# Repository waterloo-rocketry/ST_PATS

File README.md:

# ST PATS
Stpats is a system that tracks the location of the rocket and tells us where
and which direction to go to find it.

There are two modes of operation: serial and radio. In serial mode, GPS
coordinate is received from USB serial; in radio mode, GPS coordinate is
received from the radio module.

## Calibration
The on-board compass needs to be calibrated when a firmware is flashed or when
using stpats in a new environment. The compass will not work correctly without
calibration. To enter calibration mode, press the left button. The min/max
value of each axis should appear on the top left of the screen. Rotate the
whole device in every direction so the numbers stabilize, the press the left
button again to save the calibration.

## Radio Telemetry
The radio and serial mode can be toggled using the right button. At the time of
writing, the live telemetry is not done yet, so I used an Arduino to send fake
coordinates at 57600 baud to test serial reading and parsing. In theory,
plugging in configured live telemetry breakout should just work. In reality,
who knows.

## Serial Telemetry
As an alternative to radio telemetry, USB serial can also be used to send GPS
coordinate to stpats. The serial mode can be switched to using the right
button. The GPS message has the format of `[0-9]+.[0-9]*[NSEWM]`, for example:
`12.34N56.78W90M` means 12.34 degrees north, 56.78 degrees west, 90m high. The
altitude information is not used in the calculations so it’s optional.

## aprs2stpats.py
`utils/aprs2stpats.py` can be used to send APRS coordinates to stpats. To use,
install aprspy and bitstring using pip, then follow the steps in
[Receiving APRS Packet](https://uwaterloo.atlassian.net/wiki/spaces/ROCKETRY/pages/43003445444)
to setup and run direwolf TNC as a KISS server.

`usage: aprs2stpats.py [-h] [-H HOST] [-p PORT] [-c CALLSIGN] [-o OUTPUT] [--debug]`

The --host and --port options specifies the KISS TNC server to connect to. By
default, they are 127.0.0.1:8001, which connects to a direwolf instance running
on localhost.

The --callsign option filters the message by sender’s callsign, in case there
are multiple APRS beacons on the same frequency. Note the callsign includes
ssid, for example, VE7OIR-1 instead of just VE7OIR. By default, it forwards all
GPS messages.

The --output option specified the output. By default it is stdout. To send the
output to serial, use --output \\.\COM1 (Windows) or --output /dev/ttyACM0
(Linux), change COM1 or ACM0 to the actual serial port stpats is on.

The --debug options prints additional info to stderr.

## Persistent Location
Press the middle button in either mode to save the current tracking location in
flash so a reset doesn’t lose it. Most useful when one wants to unplug stpats
from computer in serial mode, pressing the middle button before disconnecting
allows one to move around without worrying losing track in case of accidental
reset.

Note: similar to calibration data, flashing a firmware wipes the flash and so
the saved data.

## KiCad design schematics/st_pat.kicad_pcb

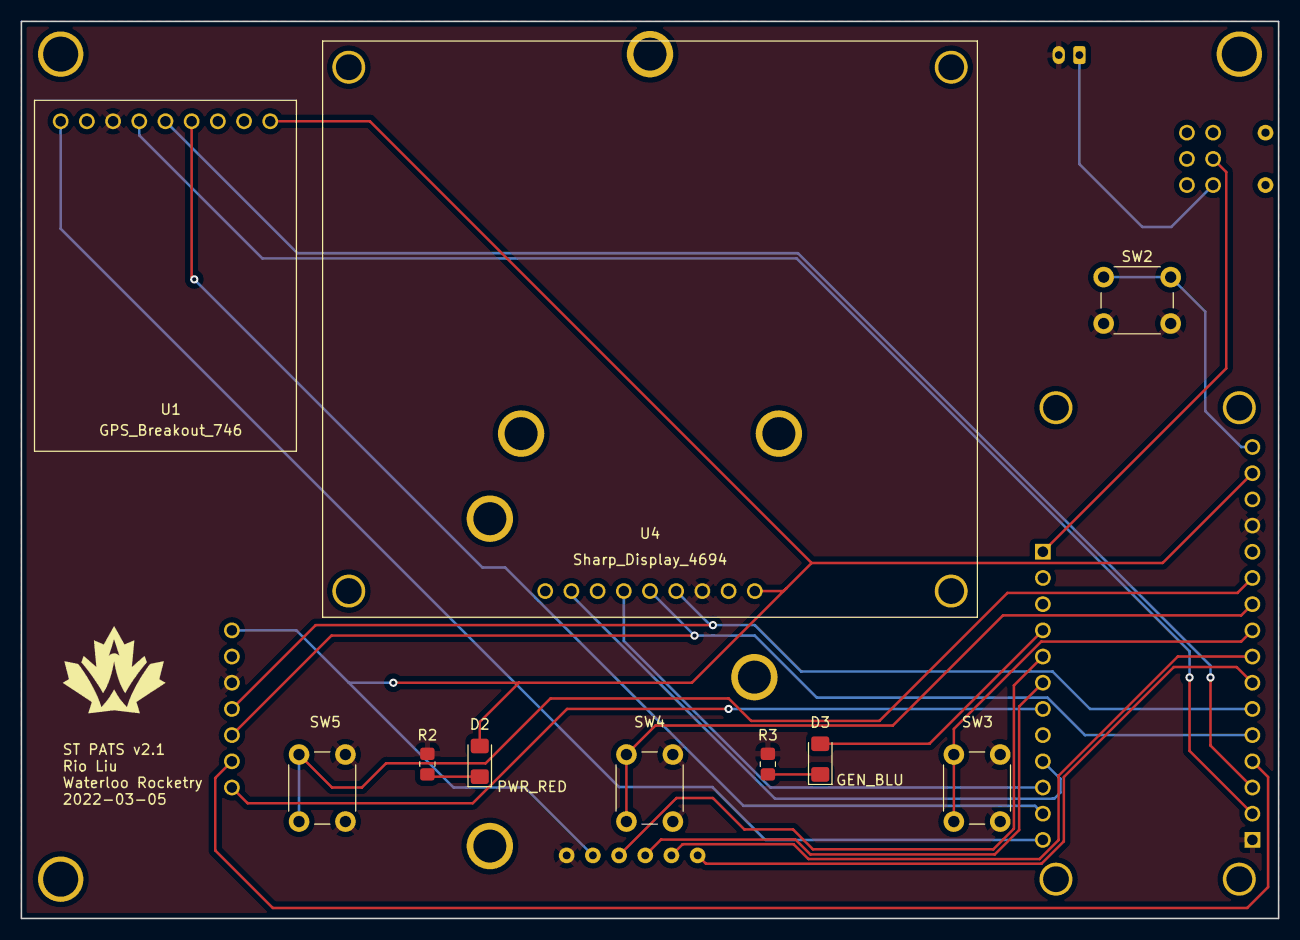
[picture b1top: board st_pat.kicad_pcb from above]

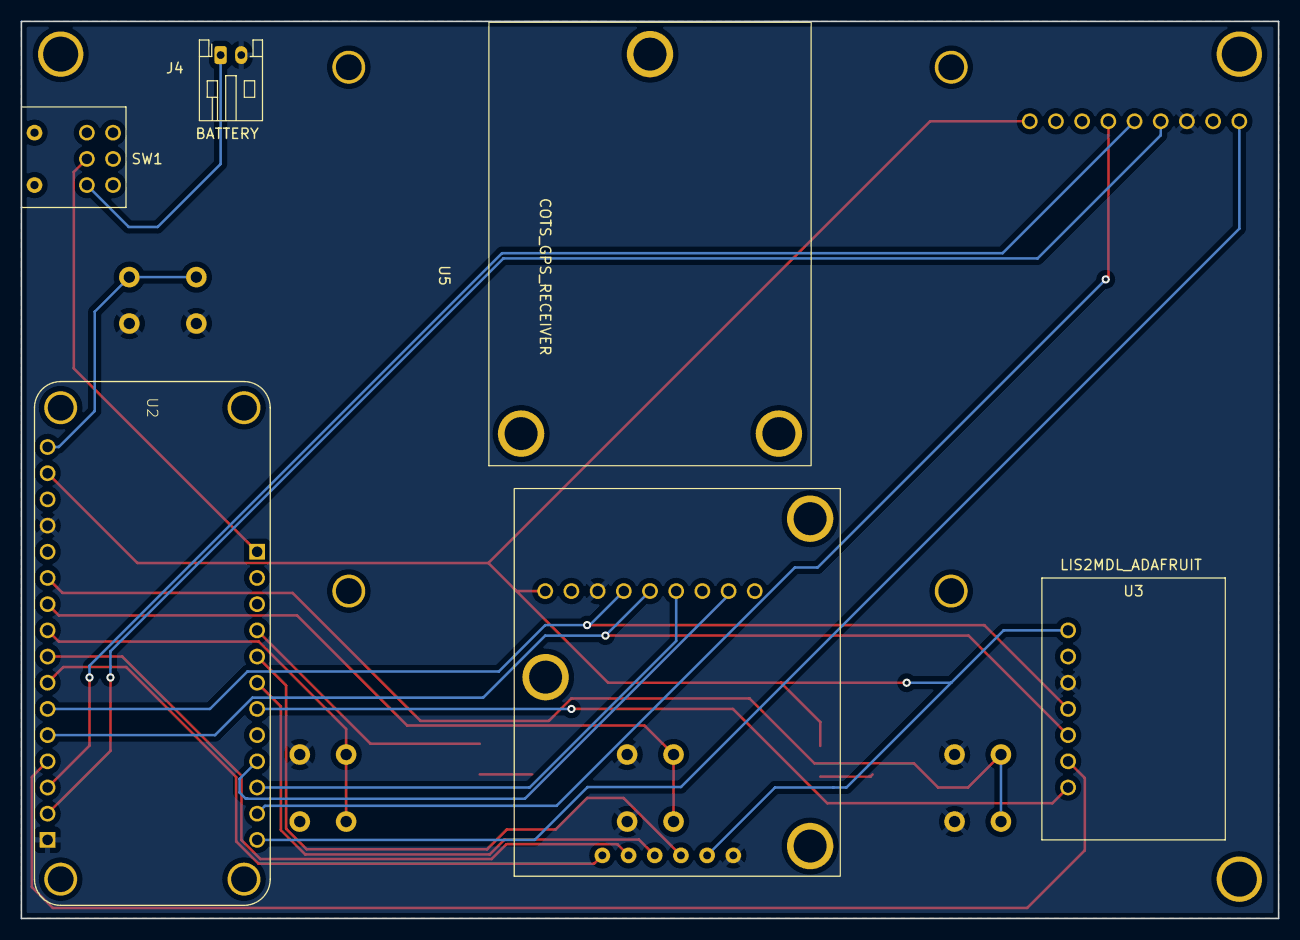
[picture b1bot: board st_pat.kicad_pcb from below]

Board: 2 copper layers, 121.9 x 87.0 mm, 15 parts (5 on the bottom side), 25 nets.

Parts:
D2: PWR_RED; LED_1206_3216Metric_Pad1.42x1.75mm_HandSolder
D3: GEN_BLU; LED_1206_3216Metric_Pad1.42x1.75mm_HandSolder
J4: BATTERY; JST_PH_S2B-PH-K_1x02_P2.00mm_Horizontal
R2: 160; R_0805_2012Metric_Pad1.20x1.40mm_HandSolder
R3: 100; R_0805_2012Metric_Pad1.20x1.40mm_HandSolder
SW1: SW_PWR; SW_Rocker_A22K1H-EA
SW2: BTN_RST; SW_PUSH_6mm
SW3, SW4, SW5: BTN; SW_PUSH_6mm
U1: GPS_Breakout_746
U2: FEATHER_M0_BASIC_PROTO
U3: LIS2MDL_ADAFRUIT; LIS3MDL_ADAFRUIT
U4: Sharp_Display_4694; Sharp_Display
U5: COTS_GPS_RECEIVER; Telemetry_Breakout

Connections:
+3V3: D2.2 (A), U1.9 (3v3), U2.P1_15 (3V3), U3.1 (VCC), U4.1 (VIN), U5.5 (VCC)
+BATT: SW1.5 (B), U2.P2_1 (VBAT)
/BTN_A1: SW5.1, U2.P1_11 (AIN2/EINT/PB08)
/BTN_A2: SW4.1, U2.P1_10 (AIN3/EINT/PB09)
/BTN_A3: SW3.1, U2.P1_9 (AIN4/VREFB/EINT/PA04)
/CPS_CS_D10: U2.P2_7 (PA18/EINT), U3.7 (CS)
/GPS_FIX_D21: U1.6 (FIX), U2.P2_11 (PA23/EINT/I2C/SCL)
/GPS_PPS_D20: U1.1 (PPS), U2.P2_12 (PA22/EINT/I2C/SDA)
/GPS_RX: U1.4 (RX), U2.P1_2 (TX/I2SCK/EINT/PA10)
/GPS_TX: U1.5 (TX), U2.P1_3 (RX/I2SF0/EINT/PA11)
/MISO: U2.P1_4 (MISO/I2C/PA12), U3.6 (SDO)
/MOSI: U2.P1_5 (MOSI/I2SMC/EINT/PB10), U3.5 (SDA), U4.5 (SI)
/RST: SW2.1, U2.P1_16 (~RESET)
/SCK: U2.P1_6 (SCK/I2SCL/EINT/PB11), U3.4 (SCL), U4.4 (SCLK)
/SHARP_CS_D5: U2.P2_10 (PA15/EINT), U4.6 (SCS)
/SHARP_DISP_D6: U2.P2_9 (PA20/EINT/I2SSC), U4.8 (DISP)
/TELE_CTS_A5: U2.P1_7 (AIN10/EINT/PB02), U5.1 (~CTS)
/TELE_RTS_A4: U2.P1_8 (AIN5/EINT/PA05), U5.2 (~RTS)
/TELE_RX_D12: U2.P2_6 (PA16/EINT/I2C), U5.3 (RX)
/TELE_TX_D11: U2.P2_5 (PA19/EINT/I2SD0), U5.4 (TX)
GND: J4.2, R2.2, R3.2, SW2.2, SW3.2, SW4.2, SW5.2, U1.3 (GND), U2.P1_1 (GND), U2.P1_13 (GND), U3.3 (GND), U4.3 (GND), U5.6 (GND)
unnamed: D2.1 (K), R2.1
unnamed: D3.1 (K), R3.1
unnamed: D3.2 (A), U2.P2_4 (PA17/EINT/I2C)
unnamed: J4.1, SW1.6 (C)

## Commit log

2019-04-18 First commit of ST PATS, as of this commit the code reads GPS and compass data and displays the heading to the LCD
2019-05-10 Added a class for parsing the location from the BigRedBee, worked on the GUI
2019-05-21 Added ST_PATS CAD model and currently empty compass calibration program.
2019-06-08 Put GPS on an interupt and got code to the point where it displays internal and BigRedBee GPS cordinates
2019-06-10 added suport for RocketCAN GPS and code to check button and led functionality
2019-06-13 minimum functionality acheived! still need to finish implementing distance to target, as well as internall compass and battery voltage checking but thease are lower priorities
2019-06-14 commented out arrow as it is currently useless, added magnetic declination compensation, implemented distance function, tentitively fixed BRB parsing bug
2019-06-18 adding the ability to store locations in EEPROM. Slightly improving the UI
2019-06-27 add the ability to handle large # of messages sent by BRB in debug mode
2019-07-29 add support for logging data to an sd card. Based on RLCS sd_handller. UNTESTED!!!
2019-07-29 fix bugs and test to ensure everything is working
2019-08-16 Notice that the SD card is powered by the display, so it will be turned off when the LCD is powercycled. Therefore set time between powercycles to 15min and add sd_init to the powercycle code.
2020-02-03 re-structure the SD logging so it re-opens the same file after re-booting the LCD instead of starting a new one.
2020-09-29 Revert "Delete all files."
    This reverts commit b707a886bbd1c5207979c834bcf842708338bed1.
2020-10-18 Fix code to work with version 1.9 of the STM32 core suport.
2020-10-27 add very rough initial readme.
2021-01-24 start st-pat-slim hardware
2021-01-30 Switch to use Feather M0 Adalogger board
2021-02-06 add compass to schematic
2021-02-06 Update schematic - clearer label, add capacitor to GPS
2021-02-06 Remove global tags and fix ERC
2021-02-07 Add some leds and switches
2021-02-14 Update schematic
2021-02-14 Found symbol and footprint for adafruit feather
2021-02-16 Add one more led to schematic and create pcb
2021-02-16 remove autogenerated files
2021-02-22 Add missing telemetry breakout board
2021-02-24 Rearrange board layout
2021-03-03 Redo layout and fix some small schematic issues
2021-03-03 rename hw to schematics
2021-03-06 Re add routes
2021-03-11 fix board outline
2021-05-08 add sharp display number to schematic
2021-05-13 redo board layout
2021-05-31 add power estimate to each component
2021-06-03 fix pr issues
2021-07-05 wip replacing gps module with breakout
2021-07-10 wip: redo layout and use diffrent button footprint
2021-07-18 update buttons layout and redo traces; add 3d model for adafruit feather
2021-07-28 add gps model to board
2021-07-30 increase spacing for leds
2021-09-30 add waterloo rocketry logo and generate gerber
2021-10-03 fix silkscreen position
2022-03-04 update schematics for new telemetry breakout board
2022-03-05 update display and telemetry breakout footprints
2022-03-05 fix sch review issues
2022-03-05 update telemetry breakout footprint and redo layout and routing
2022-03-05 remove old kicad files
2022-03-06 fix review issues
2022-03-07 add dimensions to board
2022-03-07 regenerate gerbers
2022-03-09 Refill out-of-date zones, regenerate gerbers
2022-03-16 new test code
2022-03-17 add graphical compass and fix fmap formula
2022-03-17 add persistant calibration data storage
2022-03-17 add local GPS location display
2022-03-17 fix decimal to degree/min/sec conversion
2022-04-03 fix typo in schematic and remove calibration test code
2022-04-03 add compass offset approximation
2022-04-03 WIP telemetry coordinate receiving
2022-04-04 buttons, and fix sprintf warnings
2022-04-04 adjust display layout
2022-04-04 better looking arrow
2022-04-04 update gps degree calculation
2022-04-04 fix heading calculation
2022-04-04 use fixed point field when returning gps
2022-04-14 add a aprs kiss to stpats serial script
2022-04-14 fix aprs parsing and com port open flags
2022-04-18 add rts, cts lines to telemetry serial definition
2022-04-19 remoce old step
2022-04-19 make button 2 save current coordinate
2022-04-19 use led to show receive status
2022-04-21 add radio telemetry parsing
2022-04-25 display last received time in telemetry window
2022-04-25 use 2 bytes to receive gps dmin
2022-04-26 remove debug comment
2022-04-26 reduce serial timeout
2022-04-26 actually use telemetry serial
2022-04-26 fix telemetry serial
2022-04-26 add create_gps_message function for reference
2022-04-26 improve display layout
2022-04-26 read multiple telemetry packets in same update loop
2022-05-01 remove dedfault callsign filter
2022-05-22 Add more comments, and use argparse in utils/aprs2stpats.py
2022-05-22 Add readme
2022-05-23 get rid of global args variable from aprs2stpats.py
2022-06-04 update telemetry radio to new canbus format
2022-06-04 add battery voltage monitor
2022-06-04 adjust display formats
2022-06-04 only read gps message when there are enough data in buffer
2022-06-04 increase telemetry serial throughput
2022-06-04 display gps til decimal minutes instead of seconds
2022-06-04 check for message id before sscanf and ignore board id
2022-06-23 add distance and numsats display
2022-06-23 add a home point finder
2022-06-23 fix different tele mode overwriting, fix distance calc
2022-06-24 make st_pats act as serial gps device
2023-06-19 wip: binary telemetry support
2024-08-04 binary telemetry support
2024-08-04 Update telemetry sid mask
2024-08-17 ignore 0 coordinates
2024-08-19 Add workaround for processor board's reversed gps coordinate
2025-08-01 Made Changes to Telemetry for CAN2.0B Format update. Updated untill the USB serial section in telemetry.cpp
2025-08-17 Fixed Code by Increasing Buffer Size (thx Rio). Also made telemetry write to serial output to capture messages on parsley when plugged into laptop. Allows for storage of last rocket coordinates easil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
2025-08-19 Allowed STPATS to act as an RFD LTT Source by addi ng necessary changes to telemetry.cpp, and changed serial write to allow sending of messages
